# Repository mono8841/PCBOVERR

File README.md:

# PCBOVERR
 FINAL GO BEFORE I LOSE MY MIND

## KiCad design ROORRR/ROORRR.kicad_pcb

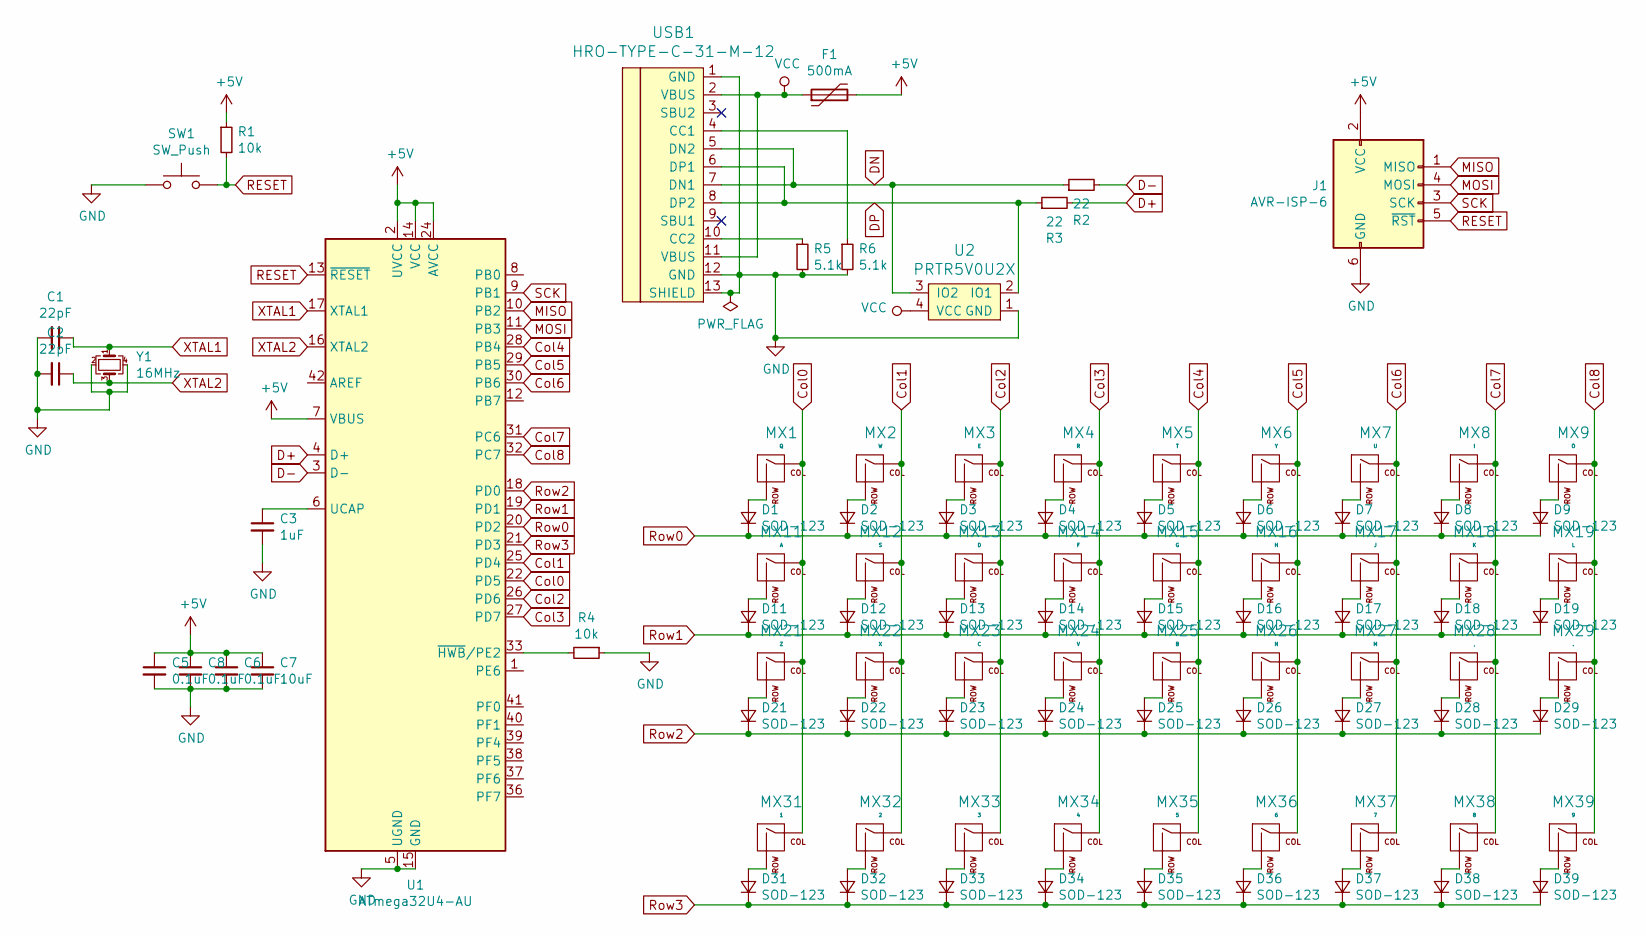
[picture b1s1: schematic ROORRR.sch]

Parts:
C1, C2: 22pF; C_0805_2012Metric_Pad1.15x1.40mm_HandSolder
C3: 1uF; C_0805_2012Metric_Pad1.15x1.40mm_HandSolder
C5, C6, C8: 0.1uF; C_0805_2012Metric_Pad1.15x1.40mm_HandSolder
C7: 10uF; C_0805_2012Metric_Pad1.15x1.40mm_HandSolder
D1, D2, D3, D4, D5, D6, D7, D8, D9, D11, D12, D13, D14, D15, D16, D17, D18, D19, D21, D22, D23, D24, D25, D26, D27, D28, D29, D31, D32, D33, D34, D35, D36, D37, D38, D39: SOD-123; D_SOD-123
F1: 500mA; Fuse_1206_3216Metric_Pad1.42x1.75mm_HandSolder
J1: AVR-ISP-6; Reset_Pretty-Mask
MX1: Q; MX-1U
MX2: W; MX-1U
MX3: E; MX-1U
MX4: R; MX-1U
MX5: T; MX-1U
MX6: Y; MX-1U
MX7: U; MX-1U
MX8: I; MX-1U
MX9: O; MX-1U
MX11: A; MX-1U
MX12: S; MX-1U
MX13: D; MX-1U
MX14: F; MX-1U
MX15: G; MX-1U
MX16: H; MX-1U
MX17: J; MX-1U
MX18: K; MX-1U
MX19: L; MX-1U
MX21: Z; MX-1U
MX22: X; MX-1U
MX23: C; MX-1U
MX24: V; MX-1U
MX25: B; MX-1U
MX26: N; MX-1U
MX27: M; MX-1U
MX28: ,; MX-1U
MX29: .; MX-1U
MX31: 1; MX-1U
MX32: 2; MX-1U
MX33: 3; MX-1U
MX34: 4; MX-1U
MX35: 5; MX-1U
MX36: 6; MX-1U
MX37: 7; MX-1U
MX38: 8; MX-1U
MX39: 9; MX-1U
R1, R4: 10k; R_0805_2012Metric_Pad1.15x1.40mm_HandSolder
R2, R3: 22; R_0805_2012Metric_Pad1.15x1.40mm_HandSolder
R5, R6: 5.1k; R_0805_2012Metric_Pad1.15x1.40mm_HandSolder
SW1: SW_Push; SKQG-1155865
U1: ATmega32U4-AU; TQFP-44_10x10mm_P0.8mm
U2: PRTR5V0U2X; SOT143B
USB1: HRO-TYPE-C-31-M-12
Y1: 16MHz; Crystal_SMD_3225-4Pin_3.2x2.5mm_HandSoldering

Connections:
+5V: C5.1, C6.1, C7.1, C8.1, F1.2, J1.2 (VCC), R1.1, U1.2 (UVCC), U1.7 (VBUS), U1.14 (VCC), U1.24 (AVCC), U1.34 (VCC), U1.44 (AVCC)
Col0: MX1.1 (COL), MX11.1 (COL), MX21.1 (COL), MX31.1 (COL), U1.22 (PD5)
Col1: MX2.1 (COL), MX12.1 (COL), MX22.1 (COL), MX32.1 (COL), U1.25 (PD4)
Col2: MX3.1 (COL), MX13.1 (COL), MX23.1 (COL), MX33.1 (COL), U1.26 (PD6)
Col3: MX4.1 (COL), MX14.1 (COL), MX24.1 (COL), MX34.1 (COL), U1.27 (PD7)
Col4: MX5.1 (COL), MX15.1 (COL), MX25.1 (COL), MX35.1 (COL), U1.28 (PB4)
Col5: MX6.1 (COL), MX16.1 (COL), MX26.1 (COL), MX36.1 (COL), U1.29 (PB5)
Col6: MX7.1 (COL), MX17.1 (COL), MX27.1 (COL), MX37.1 (COL), U1.30 (PB6)
Col7: MX8.1 (COL), MX18.1 (COL), MX28.1 (COL), MX38.1 (COL), U1.31 (PC6)
Col8: MX9.1 (COL), MX19.1 (COL), MX29.1 (COL), MX39.1 (COL), U1.32 (PC7)
D+: R3.2, U1.4 (D+)
D-: R2.2, U1.3 (D-)
DN: R2.1, U2.3 (IO2), USB1.5 (DN2), USB1.7 (DN1)
DP: R3.1, U2.2 (IO1), USB1.6 (DP1), USB1.8 (DP2)
GND: C1.2, C2.2, C3.2, C5.2, C6.2, C7.2, C8.2, J1.6 (GND), R4.1, R5.2, R6.2, SW1.1, U1.5 (UGND), U1.15 (GND), U1.23 (GND), U1.35 (GND), U1.43 (GND), U2.1 (GND), USB1.1 (GND), USB1.12 (GND), USB1.13 (SHIELD), Y1.2, Y1.4
MISO: J1.1 (MISO), U1.10 (PB2)
MOSI: J1.4 (MOSI), U1.11 (PB3)
unnamed: C3.1, U1.6 (UCAP)
unnamed: D1.2 (A), MX1.2 (ROW)
unnamed: D2.2 (A), MX2.2 (ROW)
unnamed: D3.2 (A), MX3.2 (ROW)
unnamed: D4.2 (A), MX4.2 (ROW)
unnamed: D5.2 (A), MX5.2 (ROW)
unnamed: D6.2 (A), MX6.2 (ROW)
unnamed: D7.2 (A), MX7.2 (ROW)
unnamed: D8.2 (A), MX8.2 (ROW)
unnamed: D9.2 (A), MX9.2 (ROW)
unnamed: D11.2 (A), MX11.2 (ROW)
unnamed: D12.2 (A), MX12.2 (ROW)
unnamed: D13.2 (A), MX13.2 (ROW)
unnamed: D14.2 (A), MX14.2 (ROW)
unnamed: D15.2 (A), MX15.2 (ROW)
unnamed: D16.2 (A), MX16.2 (ROW)
unnamed: D17.2 (A), MX17.2 (ROW)
unnamed: D18.2 (A), MX18.2 (ROW)
unnamed: D19.2 (A), MX19.2 (ROW)
unnamed: D21.2 (A), MX21.2 (ROW)
unnamed: D22.2 (A), MX22.2 (ROW)
unnamed: D23.2 (A), MX23.2 (ROW)
unnamed: D24.2 (A), MX24.2 (ROW)
unnamed: D25.2 (A), MX25.2 (ROW)
unnamed: D26.2 (A), MX26.2 (ROW)
unnamed: D27.2 (A), MX27.2 (ROW)
unnamed: D28.2 (A), MX28.2 (ROW)
unnamed: D29.2 (A), MX29.2 (ROW)
unnamed: D31.2 (A), MX31.2 (ROW)
unnamed: D32.2 (A), MX32.2 (ROW)
unnamed: D33.2 (A), MX33.2 (ROW)
unnamed: D34.2 (A), MX34.2 (ROW)
unnamed: D35.2 (A), MX35.2 (ROW)
unnamed: D36.2 (A), MX36.2 (ROW)
unnamed: D37.2 (A), MX37.2 (ROW)
unnamed: D38.2 (A), MX38.2 (ROW)
unnamed: D39.2 (A), MX39.2 (ROW)
unnamed: R4.2, U1.33 (~HWB~/PE2)
unnamed: R5.1, USB1.10 (CC2)
unnamed: R6.1, USB1.4 (CC1)
RESET: J1.5 (~RST), R1.2, SW1.2, U1.13 (~RESET)
Row0: D1.1 (K), D2.1 (K), D3.1 (K), D4.1 (K), D5.1 (K), D6.1 (K), D7.1 (K), D8.1 (K), D9.1 (K), U1.20 (PD2)
Row1: D11.1 (K), D12.1 (K), D13.1 (K), D14.1 (K), D15.1 (K), D16.1 (K), D17.1 (K), D18.1 (K), D19.1 (K), U1.19 (PD1)
Row2: D21.1 (K), D22.1 (K), D23.1 (K), D24.1 (K), D25.1 (K), D26.1 (K), D27.1 (K), D28.1 (K), D29.1 (K), U1.18 (PD0)
Row3: D31.1 (K), D32.1 (K), D33.1 (K), D34.1 (K), D35.1 (K), D36.1 (K), D37.1 (K), D38.1 (K), D39.1 (K), U1.21 (PD3)
SCK: J1.3 (SCK), U1.9 (PB1)
VCC: F1.1, U2.4 (VCC), USB1.2 (VBUS), USB1.11 (VBUS)
XTAL1: C1.1, U1.17 (XTAL1), Y1.1
XTAL2: C2.1, U1.16 (XTAL2), Y1.3

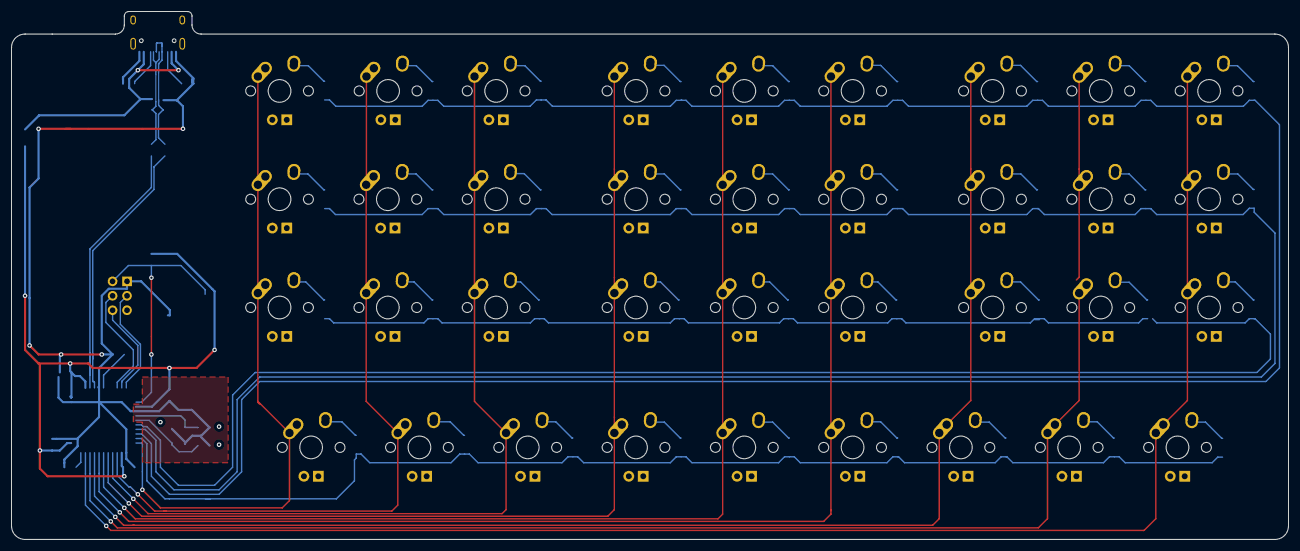
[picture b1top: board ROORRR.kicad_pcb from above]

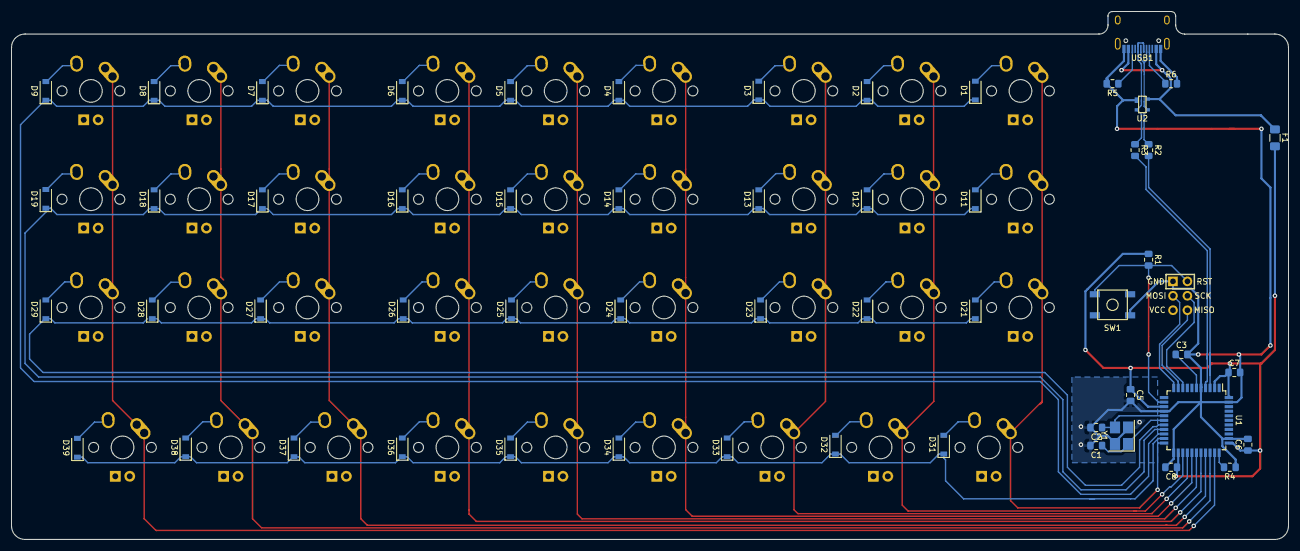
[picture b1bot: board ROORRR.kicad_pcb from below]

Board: 2 copper layers, 224.6 x 92.9 mm, 92 parts (56 on the bottom side), 66 nets.

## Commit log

2023-01-19 Add submodules
2023-01-21 checkpoint 1
2023-01-24 checkpoint 2
2023-01-24 checkpoint2
